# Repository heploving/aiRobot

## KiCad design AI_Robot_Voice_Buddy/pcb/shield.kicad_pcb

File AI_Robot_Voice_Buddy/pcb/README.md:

# Voice_Buddy 盾板 PCB

本目录是 Voice_Buddy 盾板（载板）的完整设计产物。设计说明与装配方法见 [设计说明.md](设计说明.md)。

## 文件清单

| 文件 | 说明 |
|---|---|
| shield.kicad_pcb | KiCad 6 板卡文件（可打开修改） |
| gen_pcb.py | 板卡生成脚本（Python + KiCad 6 pcbnew API） |
| export.py | 导出脚本：SVG 预览 + Gerber + 钻孔 |
| gerbers/ | 打样文件（7 层 Gerber + 2 个钻孔文件） |
| preview/ | 各层 SVG 预览（F_Cu/B_Cu/丝印/边框） |

## 重新生成（KiCad 10.0.6）

```bash
python3 gen_pcb.py                          # 生成/修改 shield.kicad_pcb
kicad-cli pcb drc --refill-zones shield.kicad_pcb   # DRC 校验
kicad-cli pcb render --side top/bottom -o preview/x.png shield.kicad_pcb  # 渲染预览
cd gerbers && kicad-cli pcb export gerbers -o . --layers F.Cu,B.Cu,F.Silkscreen,B.Silkscreen,F.Mask,B.Mask,Edge.Cuts ../shield.kicad_pcb && kicad-cli pcb export drill -o . ../shield.kicad_pcb
```

> v2 为 KiCad 10 重制版：背面整板 GND 覆铜 + 官方 DRC 校验。export.py 为
> KiCad 6 时代的旧导出脚本，已由 kicad-cli 取代，可忽略。

## 打样参数（嘉立创 JLCPCB）

- 板尺寸：62 × 64 mm，2 层，板厚 1.6mm
- 上传 gerbers/ 目录（zip 后上传或逐文件上传均可）
- 钻孔文件：shield.drl 一并上传（含 PTH/NPTH）
- 最小线宽 0.3mm、最小间距 0.2mm、最小过孔 0.4mm 孔/0.8mm 盘——常规工艺即可，无需加钱

## 元件清单

见 [设计说明.md](设计说明.md) 第 3 节（全部为直插元件，1×19 母排座 ×2 等）。

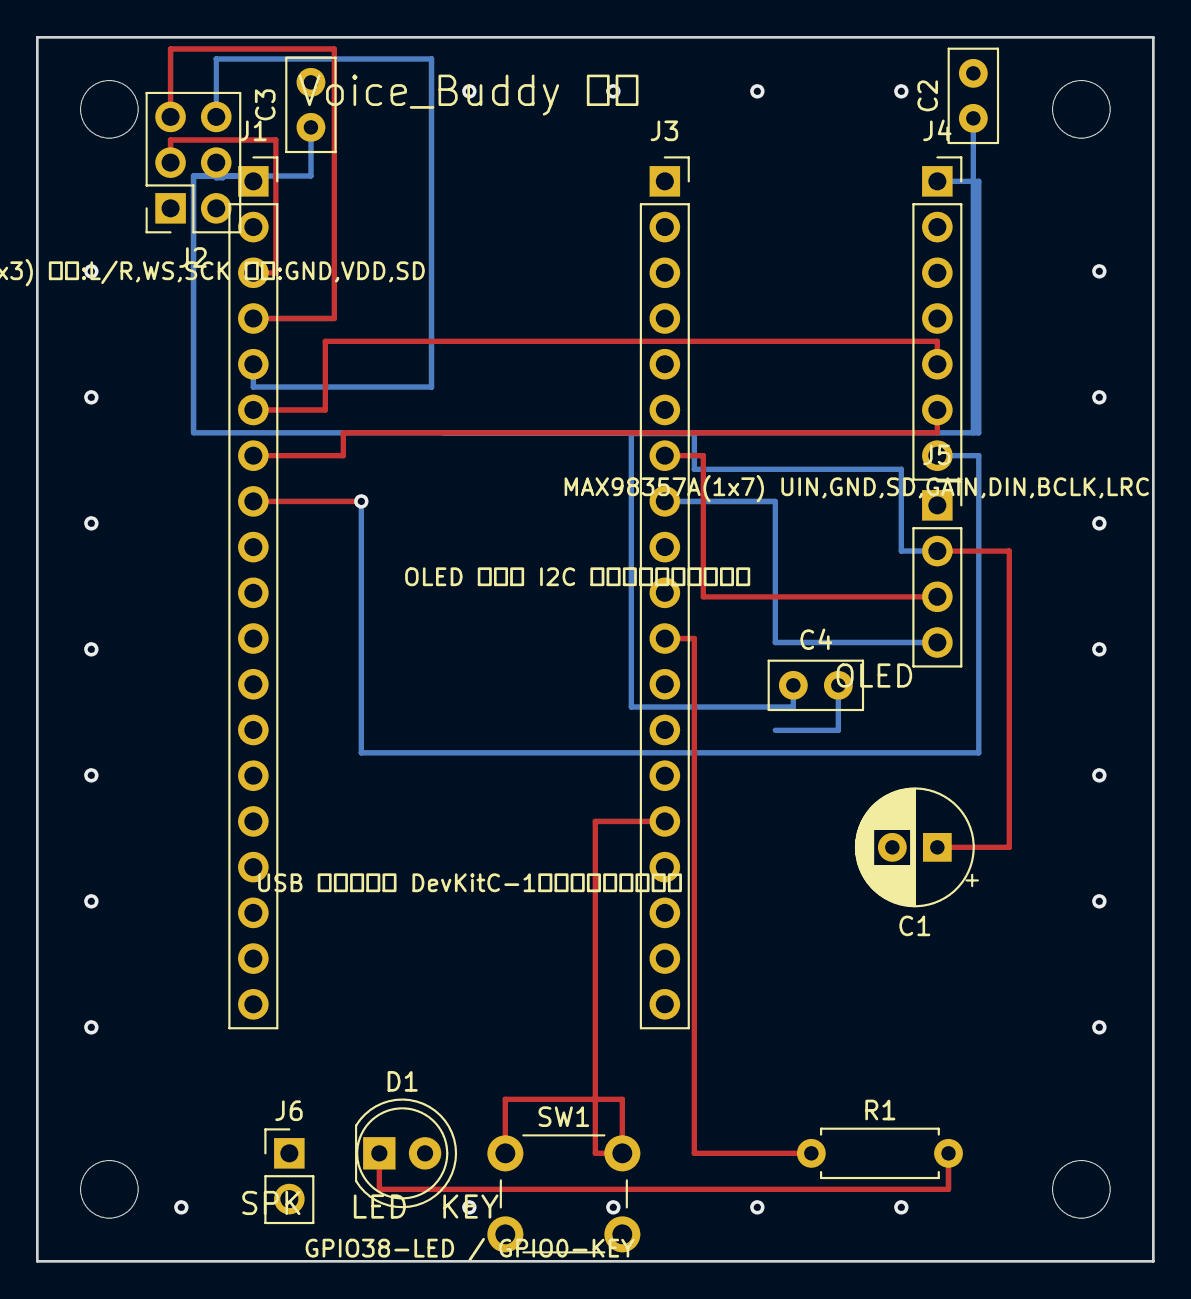
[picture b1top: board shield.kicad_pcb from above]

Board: 2 copper layers, 62.0 x 68.0 mm, 17 parts (0 on the bottom side), 13 nets.

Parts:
C1: CP_Radial_D6.3mm_P2.50mm
C2, C3, C4: C_Disc_D5.0mm_W2.5mm_P2.50mm
D1: LED_D5.0mm
H: MountingHole_3.2mm_M3
H#2, H#3, H#4: MountingHole_3.2mm_M3
J1, J3: PinSocket_1x19_P2.54mm_Vertical
J2: PinSocket_2x03_P2.54mm_Vertical
J4: PinSocket_1x07_P2.54mm_Vertical
J5: PinSocket_1x04_P2.54mm_Vertical
J6: PinHeader_1x02_P2.54mm_Vertical
R1: R_Axial_DIN0207_L6.3mm_D2.5mm_P7.62mm_Horizontal
SW1: SW_PUSH_6mm

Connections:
3V3: C1.1, C2.1, C3.1, C4.1, J1.1, J2.4, J4.1, J5.2
AMP_BCLK: J1.7, J4.6
AMP_DIN: J1.6, J4.5
AMP_LRC: J1.8, J4.7
GND: C1.2, C2.2, C3.2, C4.2, D1.2, J2.1, J2.2, J4.2, J5.1, SW1.2
KEY: J3.15, SW1.1
LED_A: D1.1, R1.2
LIGHT: J3.11, R1.1
MIC_BCLK: J1.4, J2.5
MIC_SD: J1.5, J2.6
MIC_WS: J1.3, J2.3
OLED_SCL: J3.7, J5.3
OLED_SDA: J3.8, J5.4

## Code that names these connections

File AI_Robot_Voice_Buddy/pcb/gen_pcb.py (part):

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# J2 圆形 INMP441（左列上→下 L/R,WS,SCK = pin1/3/5；右列上→下 GND,VDD,SD = pin2/4/6）
connect(J2, 1, "GND")                      # pin1 L/R 接地选左声道
connect(J2, 2, "GND")                      # pin2 GND
connect(J1, 3, "MIC_WS");   connect(J2, 3, "MIC_WS")     # pin3 WS → GPIO4
connect(J2, 4, "3V3")                                     # pin4 VDD
connect(J1, 4, "MIC_BCLK"); connect(J2, 5, "MIC_BCLK")   # pin5 SCK → GPIO5
connect(J1, 5, "MIC_SD");   connect(J2, 6, "MIC_SD")     # pin6 SD → GPIO6
# J4 MAX98357A（上→下 UIN,GND,SD,GAIN,DIN,BCLK,LRC = pin1..7）
connect(J4, 1, "3V3")                                     # pin1 UIN（3.3V 供电）
connect(J4, 2, "GND")                                    # pin2 GND
# pin3 SD 悬空（静音控制，悬空=不静音）；pin4 GAIN 悬空（默认增益）
connect(J1, 6, "AMP_DIN");  connect(J4, 5, "AMP_DIN")     # pin5 DIN → GPIO7
connect(J1, 7, "AMP_BCLK"); connect(J4, 6, "AMP_BCLK")    # pin6 BCLK → GPIO15
connect(J1, 8, "AMP_LRC");  connect(J4, 7, "AMP_LRC")     # pin7 LRC → GPIO16
# J5 SSD1306 OLED（上→下 GND,VCC,SCL,SDA）
connect(J5, 1, "GND")
connect(J5, 2, "3V3")
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path(F, 0.3, [pt(J2, 5), (pt(J2, 5)[0], 0.65), (16.5, 0.65), (16.5, 15.62), pt(J1, 4)], "MIC_BCLK")  # SCK 底边走廊
path(F, 0.3, [pt(J2, 3), (pt(J2, 3)[0], 5.7), (13.25, 5.7), (13.25, 13.08), pt(J1, 3)], "MIC_WS")   # WS
# ---- 正面：功放三线（水平走 J3 焊盘间隙，末端折入 J4 pin5/6/7）----
path(F, 0.3, [pt(J1, 6), (16, pt(J1, 6)[1]), (16, 16.89), (50, 16.89), (50, 18.16)], "AMP_DIN")      # DIN -> pin5
path(F, 0.3, [pt(J1, 7), (17, pt(J1, 7)[1]), (17, 21.97), (50, 21.97), (50, 20.7)], "AMP_BCLK")     # BCLK -> pin6
path(F, 0.3, [pt(J1, 8), (18, pt(J1, 8)[1])], "AMP_LRC")   # LRC 正面段
vlrc = pcbnew.PCB_VIA(board)
vlrc.SetPosition(P(18, 25.78))
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
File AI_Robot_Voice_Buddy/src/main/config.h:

/**
 * @file    config.h
 * @brief   全局配置头文件：硬件引脚、大模型凭据、角色设定、全部时序与业务常量
 *
 * 本文件是全项目唯一的配置点，修改任何参数只需改这里。
 *
 * 注意：
 * - 所有大模型凭据在下方对应位置填写（讯飞必填，豆包/通义/ChatGPT 可选）
 * - 标记【时序敏感】的常量与实机验证过的语音链路相关（16kHz/40ms 帧/8 倍增益），
 *   不要随意更改，改动会直接影响唤醒率与识别准确率。
 */
#pragma once

// 私密凭据（XF_APPID/XF_API_SECRET/XF_API_KEY 及各模型名/Key）不入库：
// 复制 src/main/secrets.example.h 为 src/main/secrets.h 并填写真实凭据
#if __has_include("secrets.h")
#include "secrets.h"
#else
#error "缺少 secrets.h：请复制 src/main/secrets.example.h 为 src/main/secrets.h 并填写真实凭据"
#endif

// ==================== 硬件引脚（以实机接线为准） ====================
#define KEY_PIN 0      // boot 按键引脚（上拉输入）
#define LED_PIN 48     // 板载 LED 引脚（GPIO8 已被 OLED SCL 占用）
#define LIGHT_PIN 38   // 外接灯光引脚
#define OLED_SDA 41    // SSD1306 OLED I2C 数据线
#define OLED_SCL 42    // SSD1306 OLED I2C 时钟线
#define SCREEN_WIDTH 128   // OLED 宽（像素）
#define SCREEN_HEIGHT 64   // OLED 高（像素）

// 音频放大模块（MAX98357，I2S_NUM_1）引脚
#define I2S_DOUT 7   // DIN 引脚
#define I2S_BCLK 15  // BCLK 引脚
#define I2S_LRC 16   // LRC 引脚

// 麦克风（INMP441，I2S_NUM_0）引脚
#define MIC_I2S_BCLK 5  // SCK 引脚
#define MIC_I2S_LRC 4   // WS 引脚
#define MIC_I2S_DIN 6   // SD 引脚

// ==================== 大模型参数（凭据在 secrets.h，这里只放非敏感的 API 地址） ====================
// 豆包大模型（火山方舟）
#define DOUBAO_URL "https://ark.cn-beijing.volces.com/api/v3/chat/completions"

// 通义千问大模型（阿里云百炼）
#define TONGYI_URL "https://dashscope.aliyuncs.com/compatible-mode/v1/chat/completions"

// ChatGPT（aihubmix 代理）
#define CHATGPT_URL "https://aihubmix.com/v1/chat/completions"

// ==================== 讯飞服务参数（凭据在 secrets.h） ====================

// 星火大模型 WebSocket（generalv3.5 响应更快；追求质量可换 4.0Ultra）
#define XF_SPARK_DOMAIN "generalv3.5"
#define XF_SPARK_WS "ws://spark-api.xf-yun.com/v3.5/chat"
#define XF_SPARK_HOST "spark-api.xf-yun.com"
#define XF_SPARK_PATH "/v3.5/chat"

// 讯飞语音听写（IAT）WebSocket
#define XF_IAT_WS "ws://iat-api.xfyun.cn/v2/iat"
#define XF_IAT_HOST "iat-api.xfyun.cn"
#define XF_IAT_PATH "/v2/iat"

// 讯飞 STT 语种：zh_cn 中文（支持简单英文识别），en_us 英文
#define STT_LANGUAGE "zh_cn"

// ==================== 角色设定 ====================
#define ROLE_SET "你是一个温柔的小女生，你的名字叫小白，你的性格可爱活泼，说话简短，同时温柔可爱有礼貌。"

// ==================== 语音链路时序常量【时序敏感】 ====================
#define SAMPLE_RATE_HZ 16000   // 采样率 16kHz，实测提升识别灵敏度（改采样率需同步改所有帧计数常量）
#define FRAME_MS 40            // 单帧录音时长 = 1280B / (16000Hz×2B) = 40ms
#define FRAME_BYTES 1280       // 单帧录音字节数（16bit 单声道 PCM）
#define I2S_BUF_SIZE 5120      // 一次 I2S 读入的原始字节数（= FRAME_BYTES × 4：32bit×双声道，约 40ms）
#define MIC_GAIN 8             // 麦克风数字增益倍数（信号偏弱，实测大声说话峰值仅 ~500）
#define MIC_READ_TIMEOUT_MS 100 // I2S 读超时：正常 40ms 满帧永不触发，仅硬件异常时防死等看门狗复位

// 录音噪声门限
#define NOISE_RATIO 1.8f           // 环境底噪放大系数
#define NOISE_FLOOR 300.0f         // 噪声门限下限
#define NOISE_RMS_SUPPRESS 1000    // 录音初期噪声抑制 RMS 阈值（低于此值按 8.6 处理）
#define AMBIENT_SAMPLE_COUNT 20    // 开机底噪校准采样帧数
#define AMBIENT_TRACK_START_FRAME 20 // 录音前 20 帧为初期抑制窗口，之后才开始底噪跟踪
#define SILENCE_TIMEOUT_FRAMES 250 // 10 秒静音超时（250 帧 × 40ms）
#define END_SILENCE_FRAMES 16      // 静音 16 帧（640ms）发送结束标志
#define VOICE_START_FRAMES 8       // 有声起始帧数

// ==================== 对话/播放业务常量 ====================
#define SEGMENT_SHORT_BYTES 180 // 回答超过该长度开始分段播报
#define SEGMENT_LONG_BYTES 300  // 无断句标点的超长段强制截断阈值
#define HISTORY_MAX_BYTES 800   // 对话历史总字节数上限，超出成对删除最旧问答
#define HISTORY_JSON_DOC_BYTES 1024 // 单条历史 JSON 文档容量
#define LLM_MAX_TOKENS 1024     // 大模型回复最大 token 数
#define LLM_TEMPERATURE 0.7     // 大模型采样温度
#define LLM_PRESENCE_PENALTY 1.5 // 大模型存在惩罚
#define VOLUME_MAX 100          // 最大音量
#define VOLUME_STEP 10          // 音量调节步进
#define AUTH_REFRESH_MS 240000  // 讯飞鉴权 URL 有效期（4 分钟），到期重做鉴权
#define KEY_DEBOUNCE_MS 500     // boot 按键消抖节流
#define SYNC_REQ_TIMEOUT_MS 3000 // TTS 请求发起后超时兜底（补全显示）

// 网络请求超时
#define HTTP_TIMEOUT_MS 20000          // 普通 HTTP 请求超时
#define SSE_IDLE_TIMEOUT_MS 5000       // SSE 流单行读取超时
#define STREAM_HARD_TIMEOUT_MS 120000  // SSE 流总时长硬超时
#define WIFI_ATTEMPT_MAX 30            // 单个 WiFi 重试次数
#define WIFI_ATTEMPT_DELAY_MS 100      // 重试间隔
#define TIME_SERVER_URL "https://www.baidu.com" // 从响应头 Date 获取当前时间（讯飞鉴权用）

// ==================== 网易云音乐流地址 ====================
#define NETEASE_STREAM_PREFIX "https://music.163.com/song/media/outer/url?id="
#define NETEASE_STREAM_SUFFIX ".mp3"

// ==================== 屏幕显示常量 ====================
#define CHAR_MS_CJK 190     // 中文字符估算播报时长（毫秒）
#define CHAR_MS_ASCII 90    // ASCII 字符估算播报时长（毫秒）
#define PUNCT_PAUSE_MS 250  // 标点附加停顿（毫秒）
#define CHAR_W_CJK 12       // 中文字符像素宽（12px 字体）
#define CHAR_W_ASCII 6      // ASCII 字符像素宽
#define UTF8_CJK_BYTES 3    // 中文字符 UTF-8 编码字节数
#define VOLUME_DISP_X 88    // 音量显示横坐标
